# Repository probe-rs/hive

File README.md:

# hive
Compact and modular Raspberry Pi shield for testing probe-rs

## Navigation
| Directory | Contents |
| --- | --- |
| [component_library](./component_library/) | The global hive project component library for KiCad |
| [concept](./concept/) | Concept files of this project as well as testboards, preliminary part lists etc. |
| [daughterboard](./daughterboard/) | Template of target daughterboard and existing implementations |
| [renders_3dmodels](./renders_3dmodels/) | 3D models and renders of shields |
| [shields](./shields/) | Shields needed to assemble the testing hardware |

# Overview
For more information on the assembly and the testrack itself, please have a look at the [Hive wiki](https://github.com/probe-rs/hive/wiki)

## PCB

###### Probe Shield

###### Target Stack Shield

## Assembly
The full assembly consists of 1x Raspberry Pi 4 B, 1x Probe shield and up to 8x Target stack shield. Each target stack shield can hold one daughterboard with 4 targets (not included in the pictures below). Optionally you can mount a 3D printed probe holder case to put the probes in.

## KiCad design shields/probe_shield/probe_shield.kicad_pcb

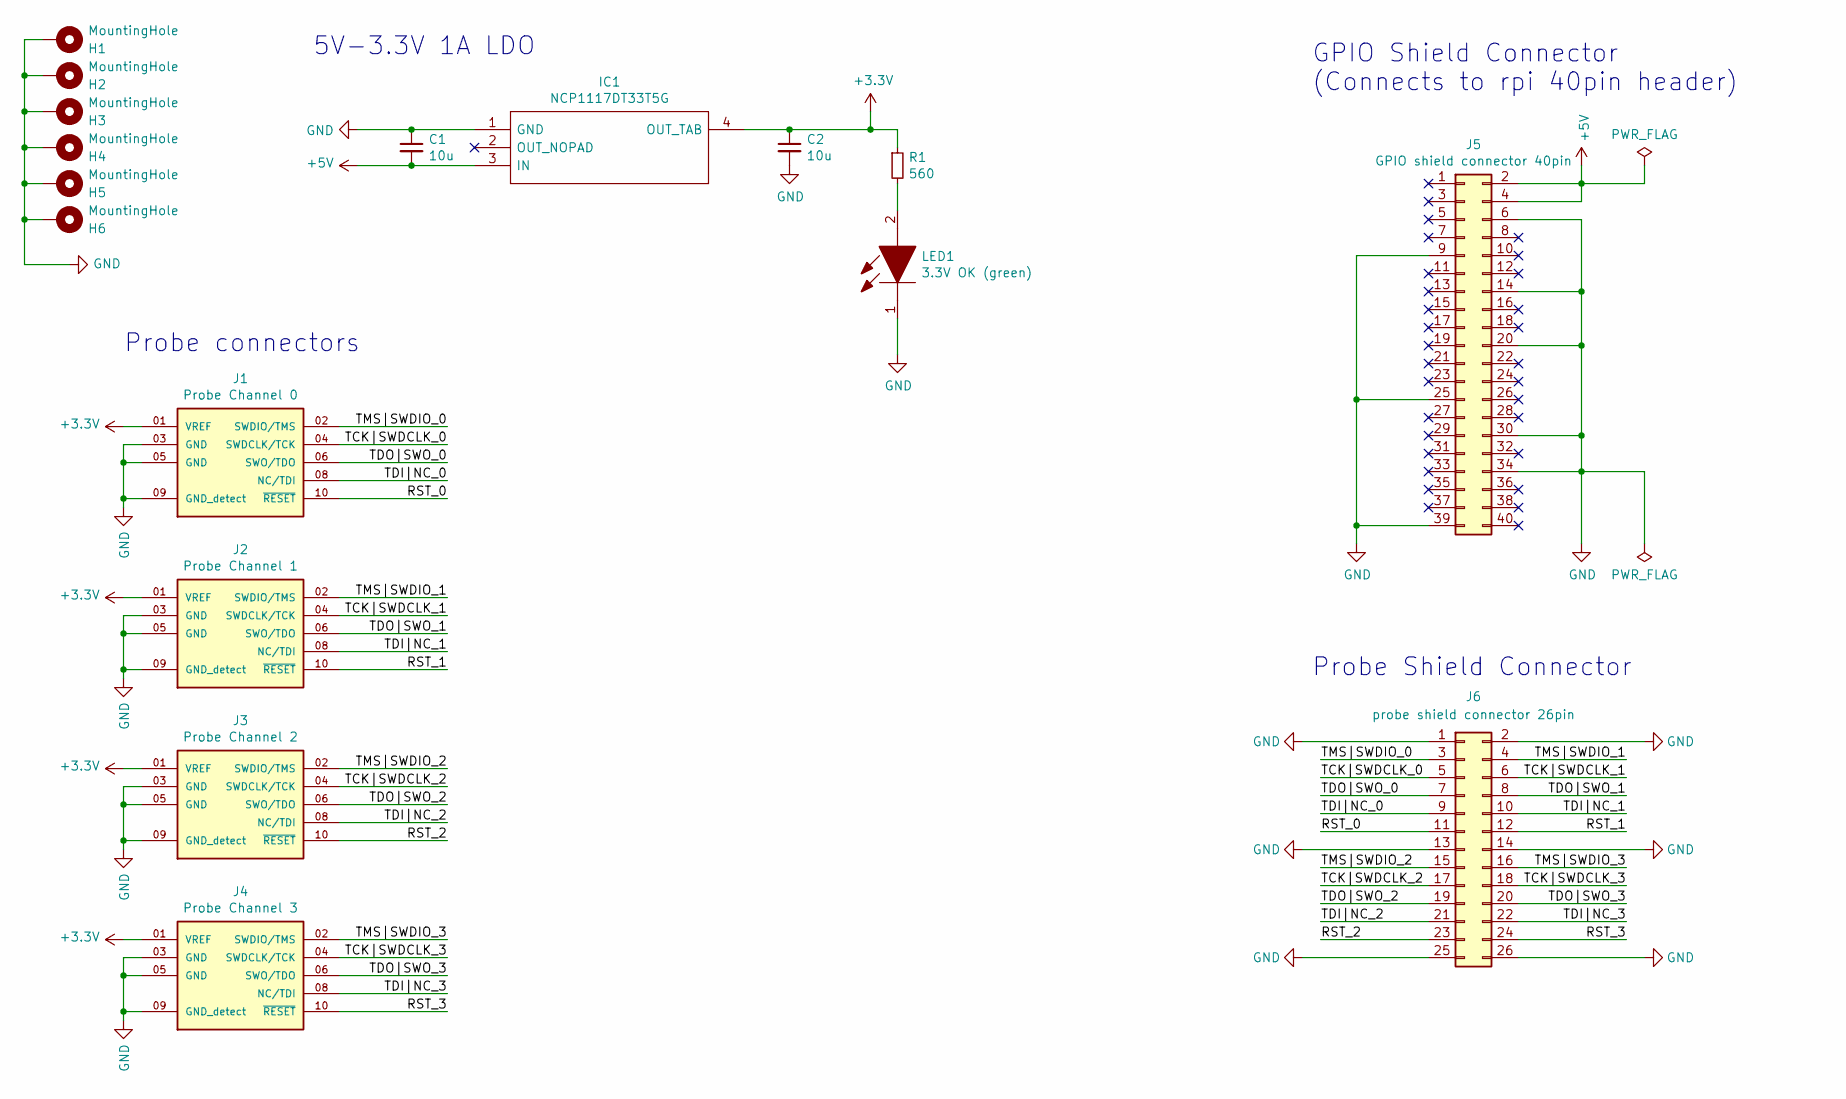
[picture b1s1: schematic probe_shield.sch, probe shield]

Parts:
C1, C2: 10u; C_0805_2012Metric_Pad1.15x1.40mm_HandSolder; Digikey Price (CHF) 0.15
H1, H2, H3, H4, H5, H6: MountingHole; MountingHole_2.7mm_M2.5_DIN965_Pad
IC1: NCP1117DT33T5G; TO229P990X238-4N; Mouser Part Number 863-NCP1117DT33T5G
J1: Probe Channel 0; SAMTEC_FTSH-105-01-F-DV-007; PARTREV R; Digikey Price (CHF) 3.56
J2: Probe Channel 1; SAMTEC_FTSH-105-01-F-DV-007; PARTREV R; Digikey Price (CHF) 3.56
J3: Probe Channel 2; SAMTEC_FTSH-105-01-F-DV-007; PARTREV R; Digikey Price (CHF) 3.56
J4: Probe Channel 3; SAMTEC_FTSH-105-01-F-DV-007; PARTREV R; Digikey Price (CHF) 3.56
J5: GPIO shield connector 40pin; PinHeader_2x20_P2.54mm_Vertical_gpio_shield; Manufacturer_Part_Number Adafruit 1979; Digikey Price (CHF) 2.74
J6: probe shield connector 26pin; PinHeader_2x13_P2.54mm_Vertical_probe_shield_male; Manufacturer_Part_Number TSW-113-07-L-D; Digikey Price (CHF) 2.01
LED1: 3.3V OK (green); LEDC1608X80N; Mouser Part Number 710-150060VS75000
R1: 560; R_0805_2012Metric_Pad1.15x1.40mm_HandSolder

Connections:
+3V3: C2.1, IC1.4 (OUT_TAB), J1.01 (VREF), J2.01 (VREF), J3.01 (VREF), J4.01 (VREF), R1.1
+5V: C1.2, IC1.3 (IN), J5.2, J5.4
/RST_0: J1.10 (~RESET~), J6.11
/RST_1: J2.10 (~RESET~), J6.12
/RST_2: J3.10 (~RESET~), J6.23
/RST_3: J4.10 (~RESET~), J6.24
/TCK|SWDCLK_0: J1.04 (SWDCLK/TCK), J6.5
/TCK|SWDCLK_1: J2.04 (SWDCLK/TCK), J6.6
/TCK|SWDCLK_2: J3.04 (SWDCLK/TCK), J6.17
/TCK|SWDCLK_3: J4.04 (SWDCLK/TCK), J6.18
/TDI|NC_0: J1.08 (NC/TDI), J6.9
/TDI|NC_1: J2.08 (NC/TDI), J6.10
/TDI|NC_2: J3.08 (NC/TDI), J6.21
/TDI|NC_3: J4.08 (NC/TDI), J6.22
/TDO|SWO_0: J1.06 (SWO/TDO), J6.7
/TDO|SWO_1: J2.06 (SWO/TDO), J6.8
/TDO|SWO_2: J3.06 (SWO/TDO), J6.19
/TDO|SWO_3: J4.06 (SWO/TDO), J6.20
/TMS|SWDIO_0: J1.02 (SWDIO/TMS), J6.3
/TMS|SWDIO_1: J2.02 (SWDIO/TMS), J6.4
/TMS|SWDIO_2: J3.02 (SWDIO/TMS), J6.15
/TMS|SWDIO_3: J4.02 (SWDIO/TMS), J6.16
GND: C1.1, C2.2, H1.1, H2.1, H3.1, H4.1, H5.1, H6.1, IC1.1 (GND), J1.03 (GND), J1.05 (GND), J1.09 (GND_detect), J2.03 (GND), J2.05 (GND), J2.09 (GND_detect), J3.03 (GND), J3.05 (GND), J3.09 (GND_detect), J4.03 (GND), J4.05 (GND), J4.09 (GND_detect), J5.6, J5.9, J5.14, J5.20, J5.25, J5.30, J5.34, J5.39, J6.1, J6.2, J6.13, J6.14, J6.25, J6.26, LED1.1
unnamed: LED1.2, R1.2

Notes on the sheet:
5V-3.3V 1A LDO
Probe connectors
GPIO Shield Connector (Connects to rpi 40pin header)
Probe Shield Connector

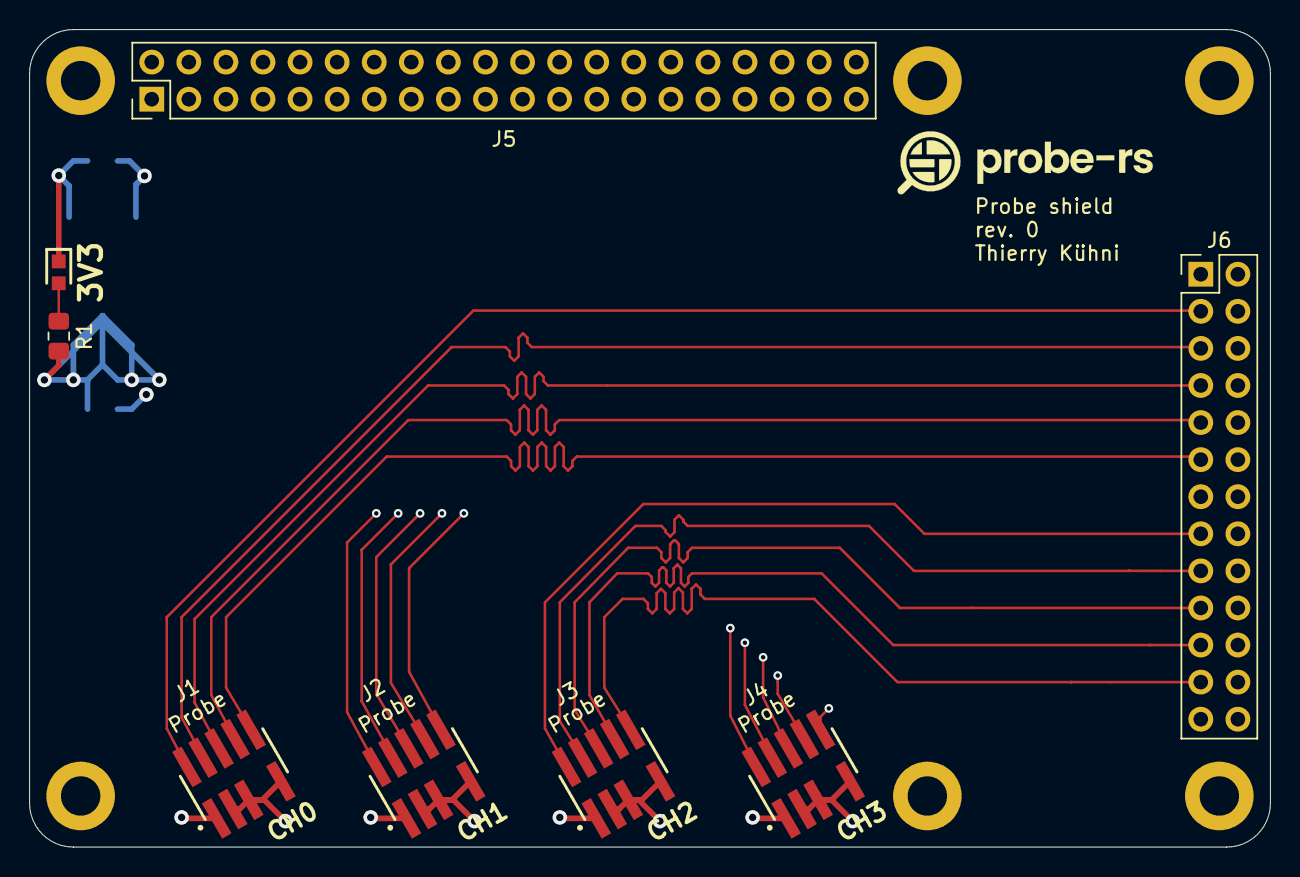
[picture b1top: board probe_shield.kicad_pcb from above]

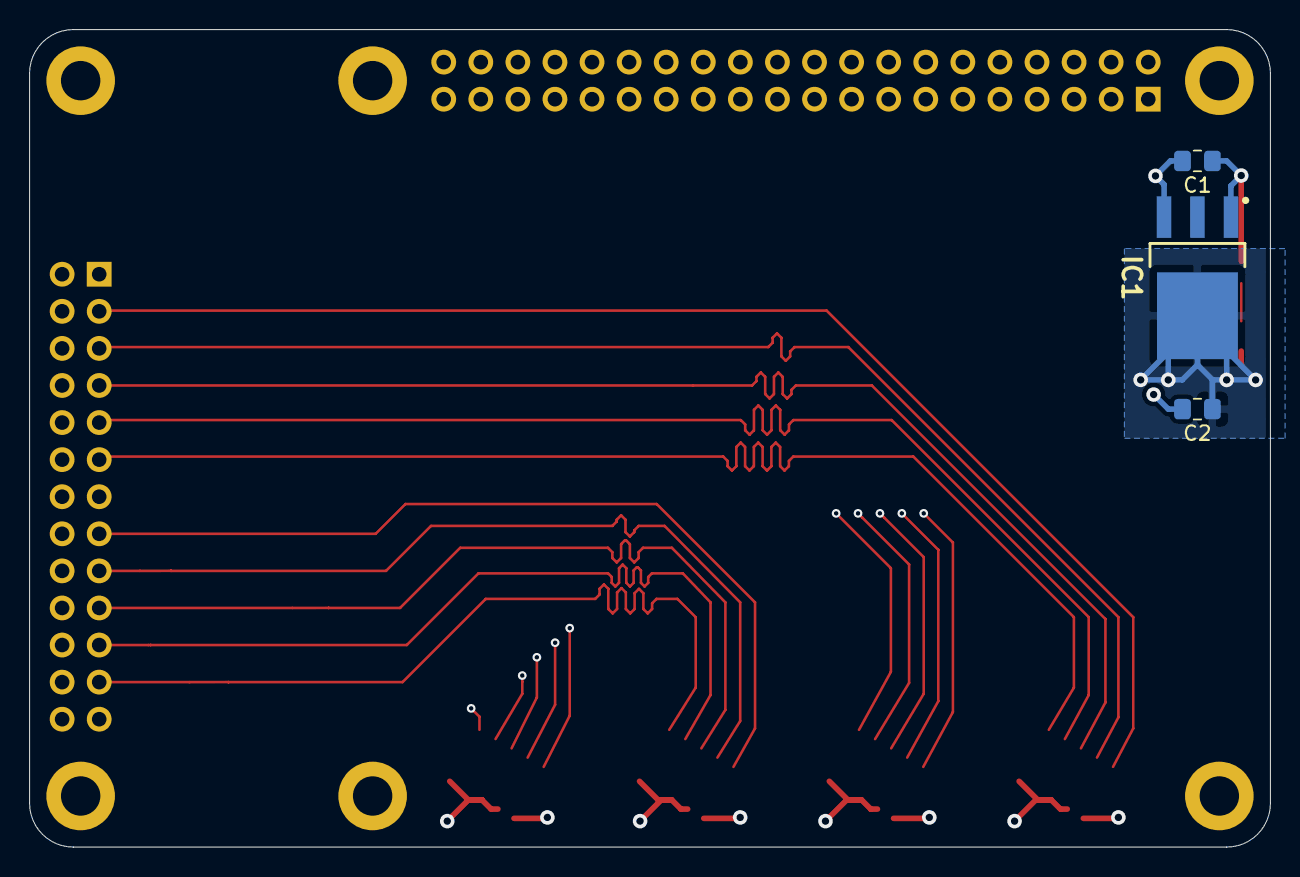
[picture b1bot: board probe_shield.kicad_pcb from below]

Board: 4 copper layers, 85.0 x 56.0 mm, 17 parts (3 on the bottom side), 24 nets.

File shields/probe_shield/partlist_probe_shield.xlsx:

Reference | Value | Manufacturer Part number | QTY | Mouser Price (CHF) | Digikey Price (CHF) | Mouser Total | Digikey Total
> C1, C2 | Capacitor 10uF | CL21A106KPFNNNF | 2 | 0.13 | 0.15 | 0.26 | 0.3
IC1 | NCP1117DT33T5G | NCP1117DT33T5G | 1 | 0.64 | 0.62 | 0.64 | 0.62
J1 | Probe Channel 0 | FTSH-105-01-F-DV-007-K | 1 | 3.61 | 3.56 | 3.61 | 3.56
J2 | Probe Channel 1 | FTSH-105-01-F-DV-007-K | 1 | 3.61 | 3.56 | 3.61 | 3.56
J3 | Probe Channel 2 | FTSH-105-01-F-DV-007-K | 1 | 3.61 | 3.56 | 3.61 | 3.56
J4 | Probe Channel 3 | FTSH-105-01-F-DV-007-K | 1 | 3.61 | 3.56 | 3.61 | 3.56
J5 | GPIO shield connector 40pin | Adafruit 1979 | 1 | 2.77 | 2.74 | 2.77 | 2.74
J6 | probe shield connector 26pin | TSW-113-07-L-D | 1 | 2.02 | 2.0099999999999998 | 2.02 | 2.0099999999999998
LED1 | 3.3V OK (green) | 150060VS75000 | 1 | 0.13 | 0.14000000000000001 | 0.13 | 0.14000000000000001
R1 | Resistor 0603 560Ohm |  | 1 | - | -
 |  |  |  |  | Total CHF | 20.259999999999998 | 20.050000000000004

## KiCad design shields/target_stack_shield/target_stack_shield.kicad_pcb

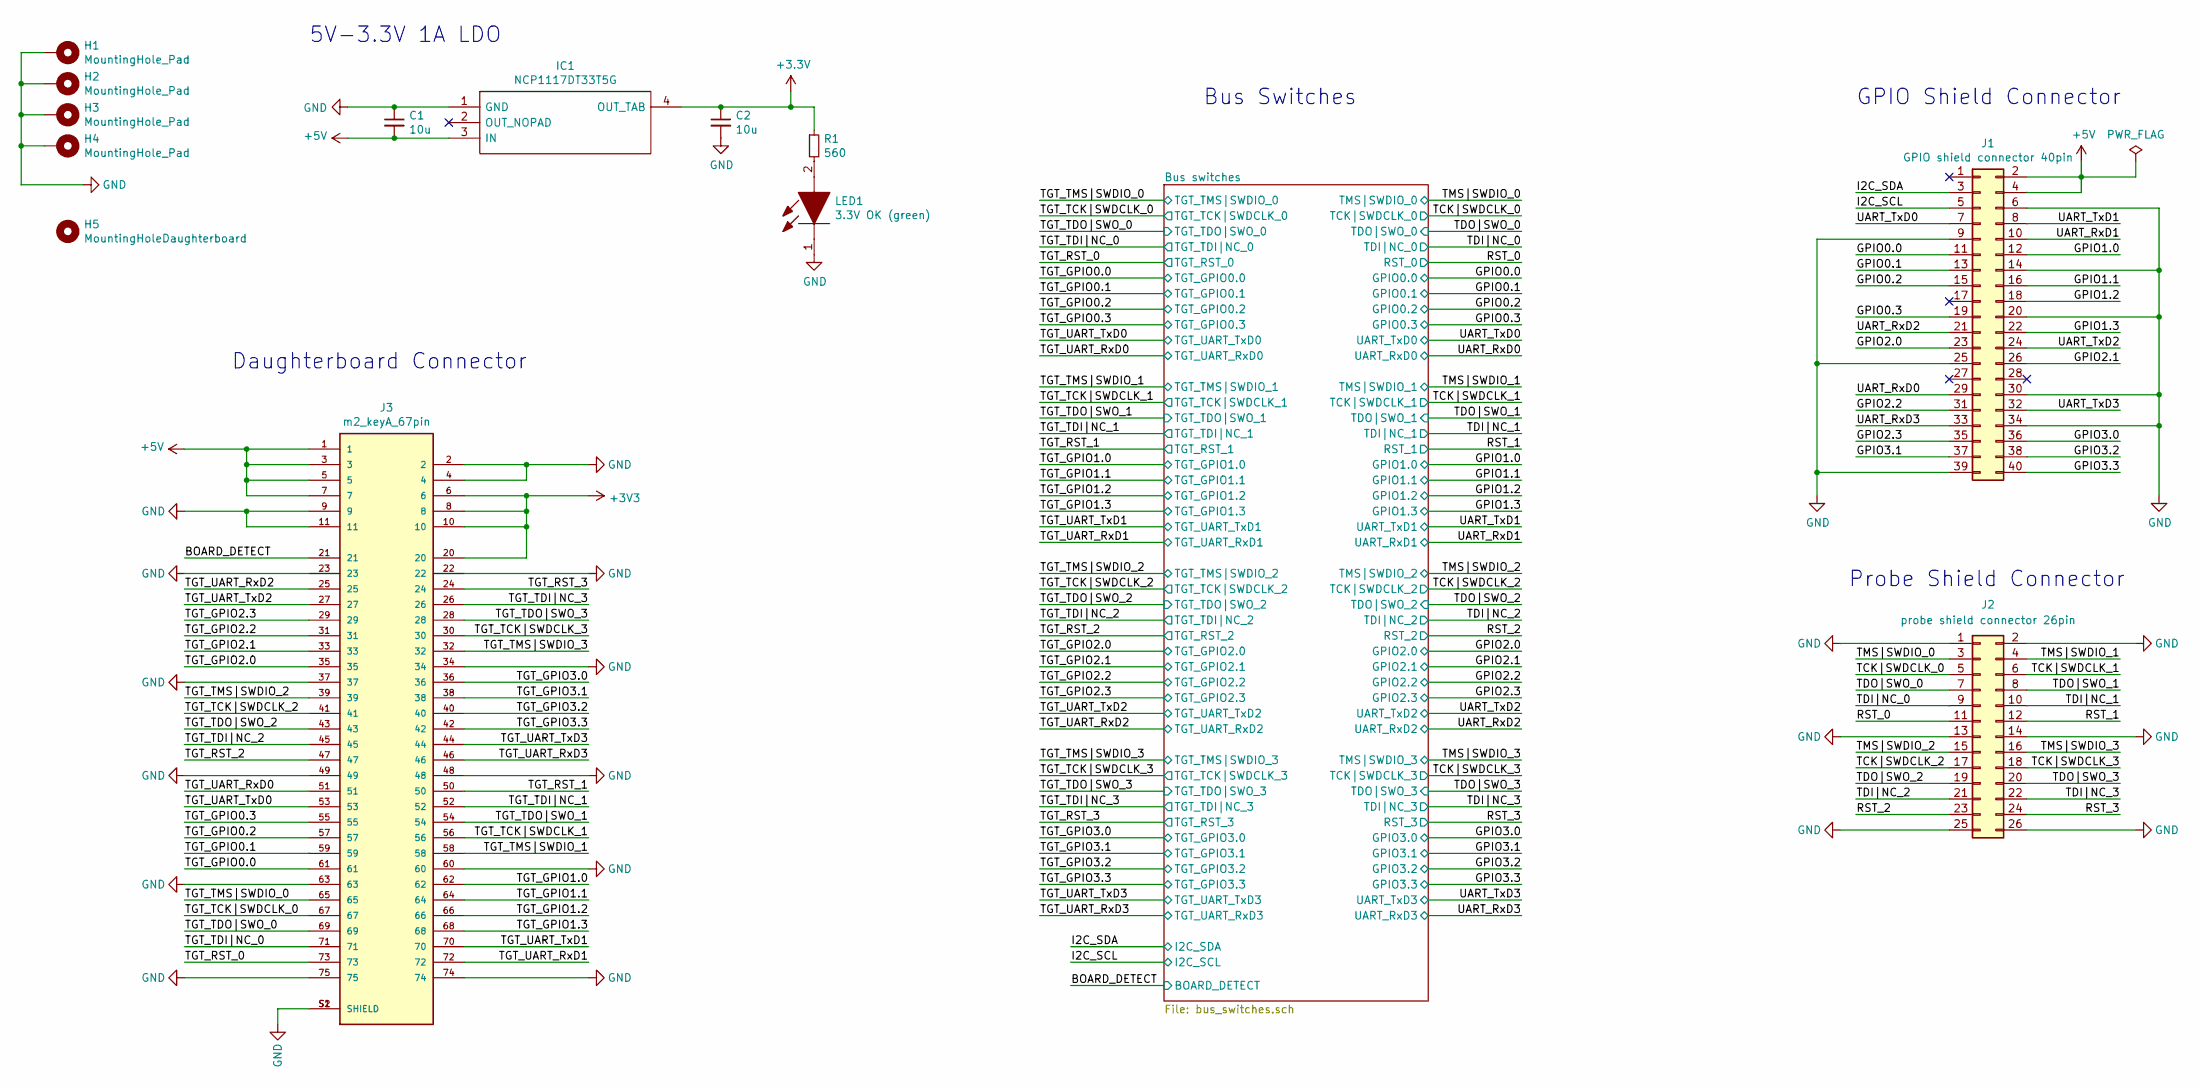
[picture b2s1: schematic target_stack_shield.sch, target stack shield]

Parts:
C1, C2: 10u; C_0805_2012Metric_Pad1.15x1.40mm_HandSolder; Manufacturer_Part_Number LMK212ABJ106MG-T; Digikey Price (CHF) 0.15
H1, H2, H3, H4: MountingHole_Pad; MountingHole_2.7mm_M2.5_DIN965_Pad
H5: MountingHoleDaughterboard; MountingHole_2.7mm_M2.5
IC1: NCP1117DT33T5G; TO229P990X238-4N; Mouser Part Number 863-NCP1117DT33T5G
J1: GPIO shield connector 40pin; PinHeader_2x20_P2.54mm_Vertical_gpio_shield; Manufacturer_Part_Number Adafruit 1979; Mouser Price (CHF) 2.77
J2: probe shield connector 26pin; PinHeader_2x13_P2.54mm_Vertical_probe_shield; Manufacturer_Part_Number Adafruit 1112; Digikey Price (CHF) 1.81
J3: m2_keyA_67pin; TE_2199230-3
LED1: 3.3V OK (green); LEDC1608X80N; Mouser Part Number 710-150060VS75000
R1: 560; R_0603_1608Metric_Pad1.05x0.95mm_HandSolder

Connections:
+5V: C1.2, IC1.3 (IN), J1.2, J1.4, J3.1, J3.3, J3.5, J3.7
/BOARD_DETECT: J3.21; also elsewhere on the board
/GPIO0.0: J1.11; also elsewhere on the board
/GPIO0.1: J1.13; also elsewhere on the board
/GPIO0.2: J1.15; also elsewhere on the board
/GPIO0.3: J1.19; also elsewhere on the board
/GPIO1.0: J1.12; also elsewhere on the board
/GPIO1.1: J1.16; also elsewhere on the board
/GPIO1.2: J1.18; also elsewhere on the board
/GPIO1.3: J1.22; also elsewhere on the board
/GPIO2.0: J1.23; also elsewhere on the board
/GPIO2.1: J1.26; also elsewhere on the board
/GPIO2.2: J1.31; also elsewhere on the board
/GPIO2.3: J1.35; also elsewhere on the board
/GPIO3.0: J1.36; also elsewhere on the board
/GPIO3.1: J1.37; also elsewhere on the board
/GPIO3.2: J1.38; also elsewhere on the board
/GPIO3.3: J1.40; also elsewhere on the board
/I2C_SCL: J1.5; also elsewhere on the board
/I2C_SDA: J1.3; also elsewhere on the board
/RST_0: J2.11; also elsewhere on the board
/RST_1: J2.12; also elsewhere on the board
/RST_2: J2.23; also elsewhere on the board
/RST_3: J2.24; also elsewhere on the board
/TCK|SWDCLK_0: J2.5; also elsewhere on the board
/TCK|SWDCLK_1: J2.6; also elsewhere on the board
/TCK|SWDCLK_2: J2.17; also elsewhere on the board
/TCK|SWDCLK_3: J2.18; also elsewhere on the board
/TDI|NC_0: J2.9; also elsewhere on the board
/TDI|NC_1: J2.10; also elsewhere on the board
/TDI|NC_2: J2.21; also elsewhere on the board
/TDI|NC_3: J2.22; also elsewhere on the board
/TDO|SWO_0: J2.7; also elsewhere on the board
/TDO|SWO_1: J2.8; also elsewhere on the board
/TDO|SWO_2: J2.19; also elsewhere on the board
/TDO|SWO_3: J2.20; also elsewhere on the board
/TGT_GPIO0.0: J3.61; also elsewhere on the board
/TGT_GPIO0.1: J3.59; also elsewhere on the board
/TGT_GPIO0.2: J3.57; also elsewhere on the board
/TGT_GPIO0.3: J3.55; also elsewhere on the board
/TGT_GPIO1.0: J3.62; also elsewhere on the board
/TGT_GPIO1.1: J3.64; also elsewhere on the board
/TGT_GPIO1.2: J3.66; also elsewhere on the board
/TGT_GPIO1.3: J3.68; also elsewhere on the board
/TGT_GPIO2.0: J3.35; also elsewhere on the board
/TGT_GPIO2.1: J3.33; also elsewhere on the board
/TGT_GPIO2.2: J3.31; also elsewhere on the board
/TGT_GPIO2.3: J3.29; also elsewhere on the board
/TGT_GPIO3.0: J3.36; also elsewhere on the board
/TGT_GPIO3.1: J3.38; also elsewhere on the board
/TGT_GPIO3.2: J3.40; also elsewhere on the board
/TGT_GPIO3.3: J3.42; also elsewhere on the board
/TGT_RST_0: J3.73; also elsewhere on the board
/TGT_RST_1: J3.50; also elsewhere on the board
/TGT_RST_2: J3.47; also elsewhere on the board
/TGT_RST_3: J3.24; also elsewhere on the board
/TGT_TCK|SWDCLK_0: J3.67; also elsewhere on the board
/TGT_TCK|SWDCLK_1: J3.56; also elsewhere on the board
/TGT_TCK|SWDCLK_2: J3.41; also elsewhere on the board
/TGT_TCK|SWDCLK_3: J3.30; also elsewhere on the board
/TGT_TDI|NC_0: J3.71; also elsewhere on the board
/TGT_TDI|NC_1: J3.52; also elsewhere on the board
/TGT_TDI|NC_2: J3.45; also elsewhere on the board
/TGT_TDI|NC_3: J3.26; also elsewhere on the board
/TGT_TDO|SWO_0: J3.69; also elsewhere on the board
/TGT_TDO|SWO_1: J3.54; also elsewhere on the board
/TGT_TDO|SWO_2: J3.43; also elsewhere on the board
/TGT_TDO|SWO_3: J3.28; also elsewhere on the board
/TGT_TMS|SWDIO_0: J3.65; also elsewhere on the board
/TGT_TMS|SWDIO_1: J3.58; also elsewhere on the board
/TGT_TMS|SWDIO_2: J3.39; also elsewhere on the board
/TGT_TMS|SWDIO_3: J3.32; also elsewhere on the board
/TGT_UART_RxD0: J3.51; also elsewhere on the board
/TGT_UART_RxD1: J3.72; also elsewhere on the board
/TGT_UART_RxD2: J3.25; also elsewhere on the board
/TGT_UART_RxD3: J3.46; also elsewhere on the board
/TGT_UART_TxD0: J3.53; also elsewhere on the board
/TGT_UART_TxD1: J3.70; also elsewhere on the board
/TGT_UART_TxD2: J3.27; also elsewhere on the board
/TGT_UART_TxD3: J3.44; also elsewhere on the board
/TMS|SWDIO_0: J2.3; also elsewhere on the board
/TMS|SWDIO_1: J2.4; also elsewhere on the board
/TMS|SWDIO_2: J2.15; also elsewhere on the board
/TMS|SWDIO_3: J2.16; also elsewhere on the board
/UART_RxD0: J1.29; also elsewhere on the board
/UART_RxD1: J1.10; also elsewhere on the board
/UART_RxD2: J1.21; also elsewhere on the board
/UART_RxD3: J1.33; also elsewhere on the board
/UART_TxD0: J1.7; also elsewhere on the board
/UART_TxD1: J1.8; also elsewhere on the board
/UART_TxD2: J1.24; also elsewhere on the board
/UART_TxD3: J1.32; also elsewhere on the board
GND: C1.1, C2.2, H1.1, H2.1, H3.1, H4.1, IC1.1 (GND), J1.6, J1.9, J1.14, J1.20, J1.25, J1.30, J1.34, J1.39, J2.1, J2.2, J2.13, J2.14, J2.25, J2.26, J3.2, J3.4, J3.9, J3.11, J3.22, J3.23, J3.34, J3.37, J3.48, J3.49, J3.60, J3.63, J3.74, J3.75, J3.S1 (SHIELD), J3.S2 (SHIELD), LED1.1; also elsewhere on the board
unnamed: LED1.2, R1.2

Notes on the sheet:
5V-3.3V 1A LDO
GPIO Shield Connector
Probe Shield Connector
Daughterboard Connector
Bus Switches

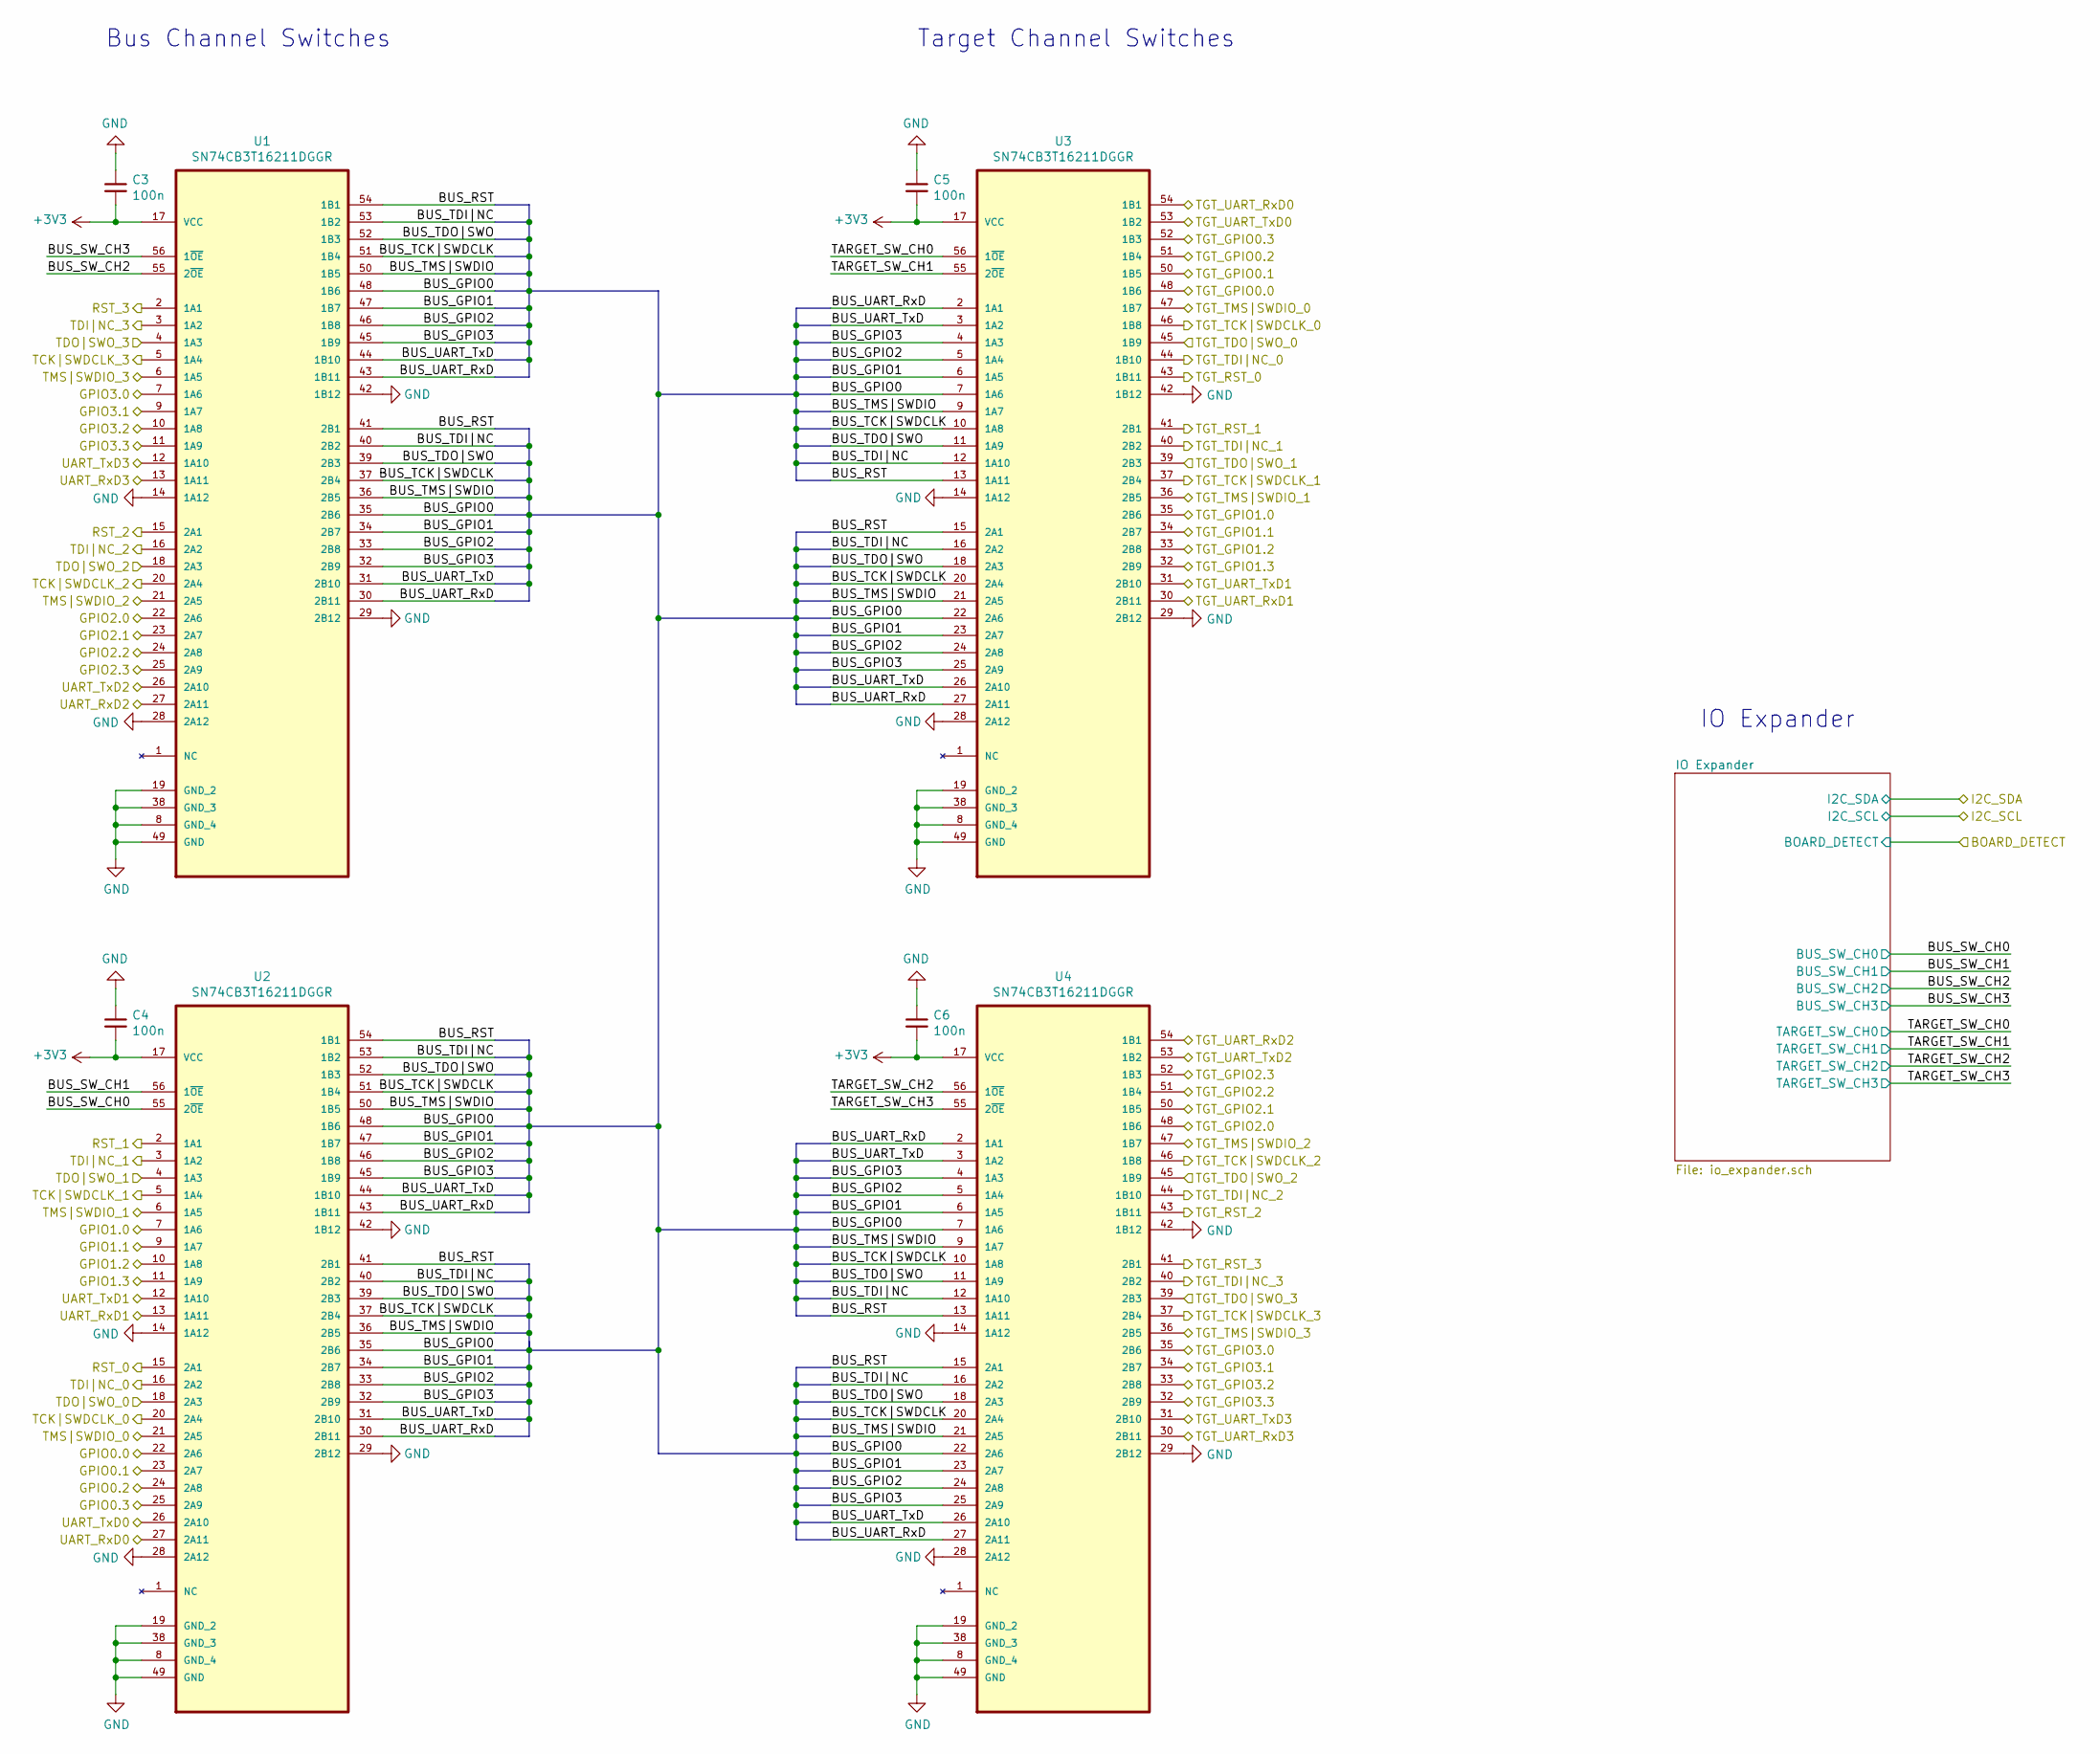
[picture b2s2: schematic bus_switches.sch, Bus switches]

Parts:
C3, C4, C5, C6: 100n; C_0603_1608Metric_Pad1.05x0.95mm_HandSolder
U1, U2, U3, U4: SN74CB3T16211DGGR; SOP50P810X120-56N; MPN SN74CB3T16211DGGR; Digikey Price (CHF) 2.64

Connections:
/Bus switches/BUS_GPIO0: U1.35 (2B6), U1.48 (1B6), U2.35 (2B6), U2.48 (1B6), U3.7 (1A6), U3.22 (2A6), U4.7 (1A6), U4.22 (2A6)
/Bus switches/BUS_GPIO1: U1.34 (2B7), U1.47 (1B7), U2.34 (2B7), U2.47 (1B7), U3.6 (1A5), U3.23 (2A7), U4.6 (1A5), U4.23 (2A7)
/Bus switches/BUS_GPIO2: U1.33 (2B8), U1.46 (1B8), U2.33 (2B8), U2.46 (1B8), U3.5 (1A4), U3.24 (2A8), U4.5 (1A4), U4.24 (2A8)
/Bus switches/BUS_GPIO3: U1.32 (2B9), U1.45 (1B9), U2.32 (2B9), U2.45 (1B9), U3.4 (1A3), U3.25 (2A9), U4.4 (1A3), U4.25 (2A9)
/Bus switches/BUS_RST: U1.41 (2B1), U1.54 (1B1), U2.41 (2B1), U2.54 (1B1), U3.13 (1A11), U3.15 (2A1), U4.13 (1A11), U4.15 (2A1)
/Bus switches/BUS_SW_CH0: U2.55 (2~OE); also elsewhere on the board
/Bus switches/BUS_SW_CH1: U2.56 (1~OE); also elsewhere on the board
/Bus switches/BUS_SW_CH2: U1.55 (2~OE); also elsewhere on the board
/Bus switches/BUS_SW_CH3: U1.56 (1~OE); also elsewhere on the board
/Bus switches/BUS_TCK|SWDCLK: U1.37 (2B4), U1.51 (1B4), U2.37 (2B4), U2.51 (1B4), U3.10 (1A8), U3.20 (2A4), U4.10 (1A8), U4.20 (2A4)
/Bus switches/BUS_TDI|NC: U1.40 (2B2), U1.53 (1B2), U2.40 (2B2), U2.53 (1B2), U3.12 (1A10), U3.16 (2A2), U4.12 (1A10), U4.16 (2A2)
/Bus switches/BUS_TDO|SWO: U1.39 (2B3), U1.52 (1B3), U2.39 (2B3), U2.52 (1B3), U3.11 (1A9), U3.18 (2A3), U4.11 (1A9), U4.18 (2A3)
/Bus switches/BUS_TMS|SWDIO: U1.36 (2B5), U1.50 (1B5), U2.36 (2B5), U2.50 (1B5), U3.9 (1A7), U3.21 (2A5), U4.9 (1A7), U4.21 (2A5)
/Bus switches/BUS_UART_RxD: U1.30 (2B11), U1.43 (1B11), U2.30 (2B11), U2.43 (1B11), U3.2 (1A1), U3.27 (2A11), U4.2 (1A1), U4.27 (2A11)
/Bus switches/BUS_UART_TxD: U1.31 (2B10), U1.44 (1B10), U2.31 (2B10), U2.44 (1B10), U3.3 (1A2), U3.26 (2A10), U4.3 (1A2), U4.26 (2A10)
/Bus switches/TARGET_SW_CH0: U3.56 (1~OE); also elsewhere on the board
/Bus switches/TARGET_SW_CH1: U3.55 (2~OE); also elsewhere on the board
/Bus switches/TARGET_SW_CH2: U4.56 (1~OE); also elsewhere on the board
/Bus switches/TARGET_SW_CH3: U4.55 (2~OE); also elsewhere on the board
/GPIO0.0: U2.22 (2A6); also elsewhere on the board
/GPIO0.1: U2.23 (2A7); also elsewhere on the board
/GPIO0.2: U2.24 (2A8); also elsewhere on the board
/GPIO0.3: U2.25 (2A9); also elsewhere on the board
/GPIO1.0: U2.7 (1A6); also elsewhere on the board
/GPIO1.1: U2.9 (1A7); also elsewhere on the board
/GPIO1.2: U2.10 (1A8); also elsewhere on the board
/GPIO1.3: U2.11 (1A9); also elsewhere on the board
/GPIO2.0: U1.22 (2A6); also elsewhere on the board
/GPIO2.1: U1.23 (2A7); also elsewhere on the board
/GPIO2.2: U1.24 (2A8); also elsewhere on the board
/GPIO2.3: U1.25 (2A9); also elsewhere on the board
/GPIO3.0: U1.7 (1A6); also elsewhere on the board
/GPIO3.1: U1.9 (1A7); also elsewhere on the board
/GPIO3.2: U1.10 (1A8); also elsewhere on the board
/GPIO3.3: U1.11 (1A9); also elsewhere on the board
/RST_0: U2.15 (2A1); also elsewhere on the board
/RST_1: U2.2 (1A1); also elsewhere on the board
/RST_2: U1.15 (2A1); also elsewhere on the board
/RST_3: U1.2 (1A1); also elsewhere on the board
/TCK|SWDCLK_0: U2.20 (2A4); also elsewhere on the board
/TCK|SWDCLK_1: U2.5 (1A4); also elsewhere on the board
/TCK|SWDCLK_2: U1.20 (2A4); also elsewhere on the board
/TCK|SWDCLK_3: U1.5 (1A4); also elsewhere on the board
/TDI|NC_0: U2.16 (2A2); also elsewhere on the board
/TDI|NC_1: U2.3 (1A2); also elsewhere on the board
/TDI|NC_2: U1.16 (2A2); also elsewhere on the board
/TDI|NC_3: U1.3 (1A2); also elsewhere on the board
/TDO|SWO_0: U2.18 (2A3); also elsewhere on the board
/TDO|SWO_1: U2.4 (1A3); also elsewhere on the board
/TDO|SWO_2: U1.18 (2A3); also elsewhere on the board
/TDO|SWO_3: U1.4 (1A3); also elsewhere on the board
/TGT_GPIO0.0: U3.48 (1B6); also elsewhere on the board
/TGT_GPIO0.1: U3.50 (1B5); also elsewhere on the board
/TGT_GPIO0.2: U3.51 (1B4); also elsewhere on the board
/TGT_GPIO0.3: U3.52 (1B3); also elsewhere on the board
/TGT_GPIO1.0: U3.35 (2B6); also elsewhere on the board
/TGT_GPIO1.1: U3.34 (2B7); also elsewhere on the board
/TGT_GPIO1.2: U3.33 (2B8); also elsewhere on the board
/TGT_GPIO1.3: U3.32 (2B9); also elsewhere on the board
/TGT_GPIO2.0: U4.48 (1B6); also elsewhere on the board
/TGT_GPIO2.1: U4.50 (1B5); also elsewhere on the board
/TGT_GPIO2.2: U4.51 (1B4); also elsewhere on the board
/TGT_GPIO2.3: U4.52 (1B3); also elsewhere on the board
/TGT_GPIO3.0: U4.35 (2B6); also elsewhere on the board
/TGT_GPIO3.1: U4.34 (2B7); also elsewhere on the board
/TGT_GPIO3.2: U4.33 (2B8); also elsewhere on the board
/TGT_GPIO3.3: U4.32 (2B9); also elsewhere on the board
/TGT_RST_0: U3.43 (1B11); also elsewhere on the board
/TGT_RST_1: U3.41 (2B1); also elsewhere on the board
/TGT_RST_2: U4.43 (1B11); also elsewhere on the board
/TGT_RST_3: U4.41 (2B1); also elsewhere on the board
/TGT_TCK|SWDCLK_0: U3.46 (1B8); also elsewhere on the board
/TGT_TCK|SWDCLK_1: U3.37 (2B4); also elsewhere on the board
/TGT_TCK|SWDCLK_2: U4.46 (1B8); also elsewhere on the board
/TGT_TCK|SWDCLK_3: U4.37 (2B4); also elsewhere on the board
/TGT_TDI|NC_0: U3.44 (1B10); also elsewhere on the board
/TGT_TDI|NC_1: U3.40 (2B2); also elsewhere on the board
/TGT_TDI|NC_2: U4.44 (1B10); also elsewhere on the board
/TGT_TDI|NC_3: U4.40 (2B2); also elsewhere on the board
/TGT_TDO|SWO_0: U3.45 (1B9); also elsewhere on the board
/TGT_TDO|SWO_1: U3.39 (2B3); also elsewhere on the board
/TGT_TDO|SWO_2: U4.45 (1B9); also elsewhere on the board
/TGT_TDO|SWO_3: U4.39 (2B3); also elsewhere on the board
/TGT_TMS|SWDIO_0: U3.47 (1B7); also elsewhere on the board
/TGT_TMS|SWDIO_1: U3.36 (2B5); also elsewhere on the board
/TGT_TMS|SWDIO_2: U4.47 (1B7); also elsewhere on the board
/TGT_TMS|SWDIO_3: U4.36 (2B5); also elsewhere on the board
/TGT_UART_RxD0: U3.54 (1B1); also elsewhere on the board
/TGT_UART_RxD1: U3.30 (2B11); also elsewhere on the board
/TGT_UART_RxD2: U4.54 (1B1); also elsewhere on the board
/TGT_UART_RxD3: U4.30 (2B11); also elsewhere on the board
/TGT_UART_TxD0: U3.53 (1B2); also elsewhere on the board
/TGT_UART_TxD1: U3.31 (2B10); also elsewhere on the board
/TGT_UART_TxD2: U4.53 (1B2); also elsewhere on the board
/TGT_UART_TxD3: U4.31 (2B10); also elsewhere on the board
/TMS|SWDIO_0: U2.21 (2A5); also elsewhere on the board
/TMS|SWDIO_1: U2.6 (1A5); also elsewhere on the board
/TMS|SWDIO_2: U1.21 (2A5); also elsewhere on the board
/TMS|SWDIO_3: U1.6 (1A5); also elsewhere on the board
/UART_RxD0: U2.27 (2A11); also elsewhere on the board
/UART_RxD1: U2.13 (1A11); also elsewhere on the board
/UART_RxD2: U1.27 (2A11); also elsewhere on the board
/UART_RxD3: U1.13 (1A11); also elsewhere on the board
/UART_TxD0: U2.26 (2A10); also elsewhere on the board
/UART_TxD1: U2.12 (1A10); also elsewhere on the board
/UART_TxD2: U1.26 (2A10); also elsewhere on the board
/UART_TxD3: U1.12 (1A10); also elsewhere on the board
GND: C3.1, C4.1, C5.1, C6.1, U1.8 (GND_4), U1.14 (1A12), U1.19 (GND_2), U1.28 (2A12), U1.29 (2B12), U1.38 (GND_3), U1.42 (1B12), U1.49 (GND), U2.8 (GND_4), U2.14 (1A12), U2.19 (GND_2), U2.28 (2A12), U2.29 (2B12), U2.38 (GND_3), U2.42 (1B12), U2.49 (GND), U3.8 (GND_4), U3.14 (1A12), U3.19 (GND_2), U3.28 (2A12), U3.29 (2B12), U3.38 (GND_3), U3.42 (1B12), U3.49 (GND), U4.8 (GND_4), U4.14 (1A12), U4.19 (GND_2), U4.28 (2A12), U4.29 (2B12), U4.38 (GND_3), U4.42 (1B12), U4.49 (GND); also elsewhere on the board

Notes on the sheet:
Bus Channel Switches
Target Channel Switches
IO Expander
